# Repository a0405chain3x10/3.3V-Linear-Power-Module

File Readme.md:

# 3.3V Linear Power Delivery Module

## Overview
This repository contains the KiCad design files for a custom 5V to 3.3V power delivery network. Built around the AMS1117-3.3 Low-Dropout (LDO) regulator, this module is designed to provide stable, filtered power for mixed-signal microcontrollers by implementing both high-frequency and bulk decoupling strategies. 

## Visuals

<br>

*(Note: Ensure image files are uploaded to the root of the repository so these links render correctly)*

## Design Highlights
* **Dual-Stage Decoupling:** Utilizes a 100µF bulk capacitor for instantaneous current spikes and a 0.1µF bypass capacitor for high-frequency noise filtration on both the input and output rails.
* **Thermal Management:** The LDO tab is coupled to a solid copper ground plane on the PCB to act as a thermal heatsink during high-current draw.
* **Trace Routing:** Calculated trace widths used for the +5V and 3V3 nets to safely handle required current without excessive voltage drop.

## Bill of Materials (BOM)

| Ref | Qty | Component Details | Package | Source Link |
| :--- | :---: | :--- | :--- | :--- |
| **C1, C3** | 2 | 0.1µF, 50V MLCC (KEMET C0805C104K5RAC7210) | SMD 0805 | [Robu.in](https://robu.in/product/c0805c104k5rac7210-kemet-cap-smd-mlcc-0-1-%C2%B5f-50-v-0805-pack-of-1/) |
| **C2, C4** | 2 | 100µF, 6.3V MLCC (MURATA 21BR60J107ME15K) | SMD 0805 | [Robu.in](https://robu.in/product/21br60j107me15k-murata-cap-smd-mlcc-100%C2%B5f-6-3-v-0805-pack-of-1/) |
| **D1** | 1 | 5mm Red DIP LED | THT 5.0mm | [Robu.in](https://robu.in/product/5mm-red-dip-led-pack-of-50/) |
| **J1, J2** | 2 | 2.54mm Pitch Male Header (Breakable) | THT 2.54mm | [Robu.in](https://robu.in/product/pcb-male-header-40-pin-kit-6-colours-5pcs-each/) |
| **R1** | 1 | 68Ω, 125mW Resistor (Yageo RC0805JR-0768RL) | SMD 0805 | [Robu.in](https://robu.in/product/rc0805jr-0768rl-yageo-smd-chip-resistor-68-ohm-%25c2%25b1-5-125-mw-0805-2012-metric-thick-film-general-purpose/) |
| **U1** | 1 | AMS1117-3.3V 1A LDO Voltage Regulator | SMD SOT-223 | [Robu.in](https://robu.in/product/ams1117-3-3v-1a-sot-223-voltage-regulator-ic-pack-of-5-ics/) |

## Fabrication Specs
* **Layers:** 2 (Front Cu, Back Cu)
* **Design Rule Check (DRC):** 0 Violations
* **EDA Tool:** KiCad 10.0

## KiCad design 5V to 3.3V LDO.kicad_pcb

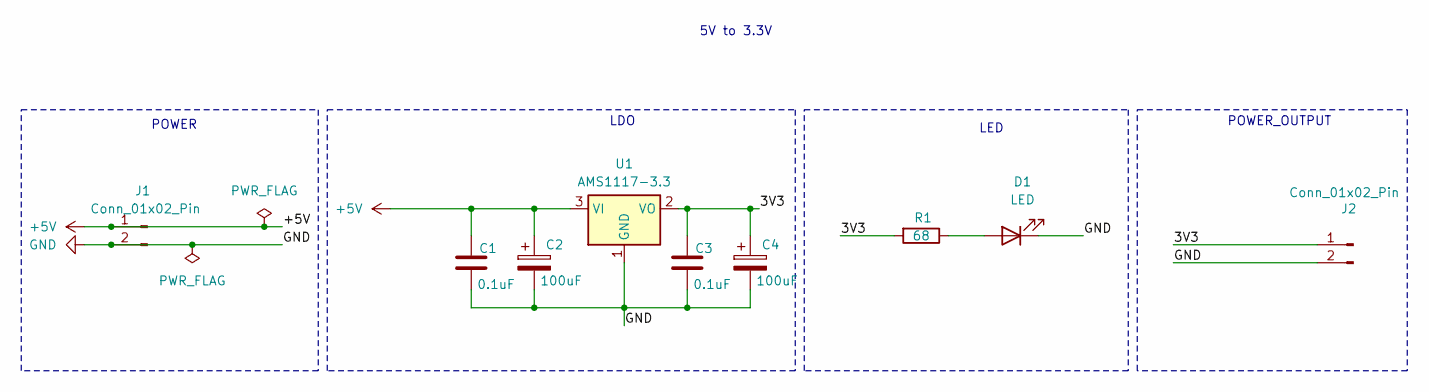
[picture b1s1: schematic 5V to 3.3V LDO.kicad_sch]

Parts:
C1, C3: 0.1uF; C_0805_2012Metric
C2, C4: 100uF; C_0805_2012Metric
D1: LED; LED_D5.0mm
J1, J2: Conn_01x02_Pin; PinHeader_1x02_P2.54mm_Vertical
R1: 68; R_0805_2012Metric
U1: AMS1117-3.3; SOT-223-3_TabPin2

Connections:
+5V: C1.1, C2.1, J1.1, U1.3 (VI)
/3V3: C3.1, C4.1, J2.1, R1.2, U1.2 (VO)
GND: C1.2, C2.2, C3.2, C4.2, D1.1 (K), J1.2, J2.2, U1.1 (GND)
unnamed: D1.2 (A), R1.1

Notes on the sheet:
LED
POWER_OUTPUT
POWER
LDO
5V to 3.3V

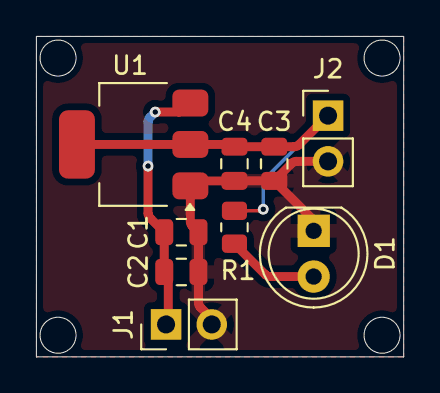
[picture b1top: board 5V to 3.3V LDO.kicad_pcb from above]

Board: 2 copper layers, 20.4 x 17.8 mm, 9 parts (0 on the bottom side), 4 nets.
